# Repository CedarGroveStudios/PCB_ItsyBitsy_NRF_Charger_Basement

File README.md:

### _A charger add-on for the ItsyBitsy NRF_

# ItsyBitsy NRF Charger Basement

## Overview
A piggybottom LiPo charger board for attaching underneath an Adafruit ItsyBitsy NRF board. A 2-pin JST LiPo battery connection is on-board that supports charging (100mA charge rate), compatible with Adafruit’s standard battery connector polarity.

ItsyBitsy Breadboard Adapter [Schematic](https://github.com/CedarGroveStudios/PCB_ItsyBitsy_NRF_Charger_Basement/blob/main/PCB/ItsyBitsy%20breadboard.pdf)

OSH Park shared project: <a href="https://oshpark.com/shared_projects/iI4kd3TW"></img></a>

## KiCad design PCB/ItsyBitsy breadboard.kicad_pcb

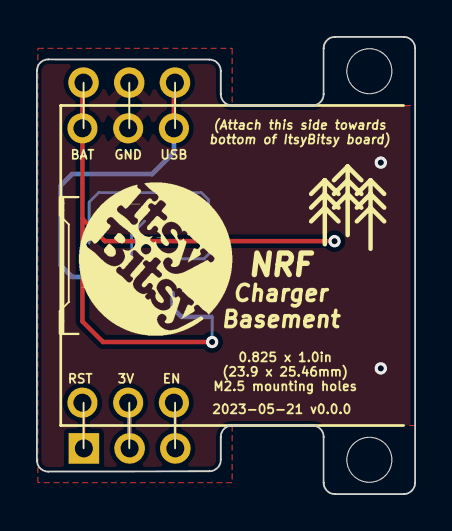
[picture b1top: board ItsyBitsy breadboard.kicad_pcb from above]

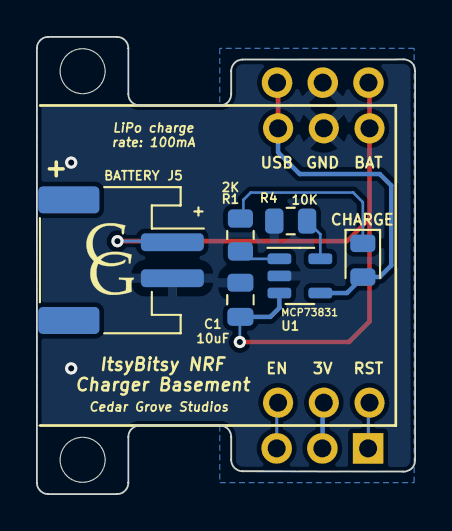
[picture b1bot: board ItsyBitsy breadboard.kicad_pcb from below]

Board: 2 copper layers, 21.0 x 25.4 mm, 11 parts (6 on the bottom side), 9 nets.

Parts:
C1: 10uF; C_0805_2012Metric
D1: CHARGE; LED_0805_2012Metric
J1, J2: Conn_01x03; PinHeader_1x03_P2.54mm_Vertical
J5: BATTERY; JST_PH_S2B-PH-SM4-TB_1x02-1MP_P2.00mm_Horizontal
M1: ItsyBitsy_M4_Express
R1: 2K; R_0805_2012Metric
R4: 10K; R_0805_2012Metric
U1: MCP73831; SOT-23-5
U$5: ItsyBitsy_logo
logo: ItsyBitsy_logo

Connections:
/3V: J2.2, M1.2 (3V)
/BAT: C1.1, J1.1, J5.1, M1.33 (BAT), U1.3 (Vbat)
/EN: J2.3, M1.3 (Aref)
/USB: D1.2 (A), J1.3, M1.31 (USB), U1.4 (Vdd)
/~RST: J2.1, M1.1 (RST)
GND: C1.2, J1.2, J5.2, M1.32 (G), R4.2, U1.2 (Vss)
unnamed: D1.1 (K), R1.1
unnamed: R1.2, U1.1 (STAT)
unnamed: R4.1, U1.5 (PROG)

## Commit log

2023-05-31 initial repo load
